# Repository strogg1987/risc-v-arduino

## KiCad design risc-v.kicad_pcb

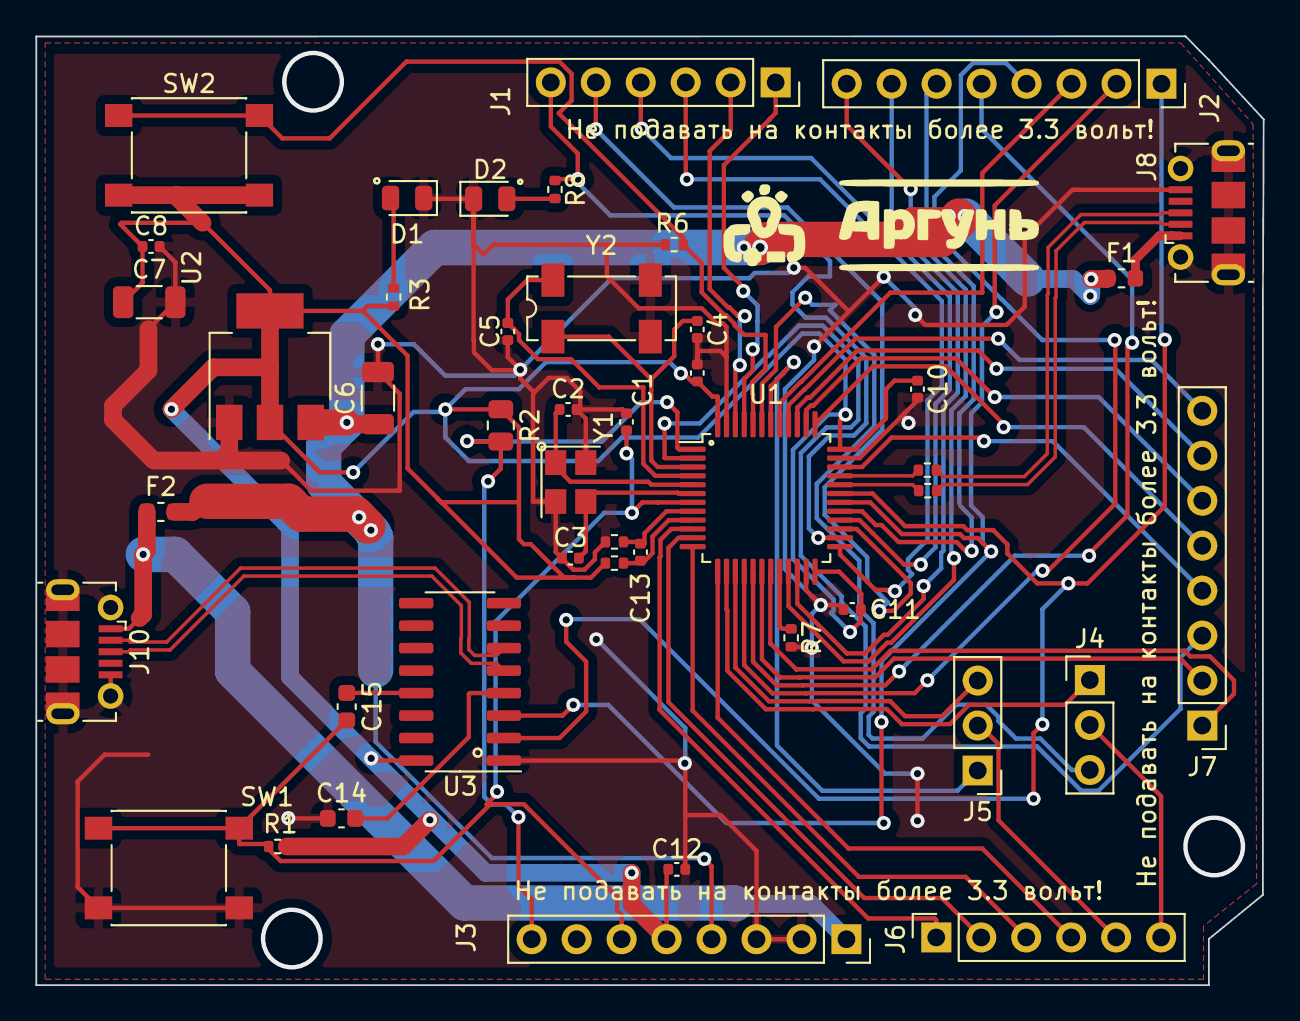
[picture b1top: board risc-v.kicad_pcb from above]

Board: 2 copper layers, 69.3 x 53.6 mm, 45 parts (0 on the bottom side), 57 nets.

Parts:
C1, C8, C9, C10, C11, C12, C13: 100nF; C_0402_1005Metric
C2, C3: 8pF; C_0402_1005Metric
C4, C5: 6pF; C_0402_1005Metric
C6, C7: 10uF; C_1206_3216Metric
C14, C15: 0.1uF; C_0603_1608Metric
D1, D2: LED; LED_0805_2012Metric
F1: 6V 2A; Fuse_0603_1608Metric
F2: Fuse_Small; Fuse_0603_1608Metric
FB1, FB2: CBW100505U601T; R_0402_1005Metric
J1: Conn_pin13:pin8; PinSocket_1x06_P2.54mm_Vertical
J2: conn_pin7:pin0; PinSocket_1x08_P2.54mm_Vertical
J3: analog5:0; PinSocket_1x06_P2.54mm_Vertical
J4: selector_a5; PinHeader_1x03_P2.54mm_Vertical
J5: selector_a4; PinHeader_1x03_P2.54mm_Vertical
J6: powerline; PinSocket_1x08_P2.54mm_Vertical
J7: extra pins; PinHeader_1x08_P2.54mm_Vertical
J8, J10: USB-FS; USB_Micro-B_Molex-105017-0001
R1, R6, R7: 10k; R_0402_1005Metric
R2: R; R_0805_2012Metric
R3, R8: 2k; R_0402_1005Metric
R4, R5: 22R; R_0402_1005Metric
SW1, SW2: SW_Push_Dual 6x6 smd; SW_Push_1P1T_NO_6x6mm_H9.5mm
U1: gd32vf103cbt6; LQFP-48_7x7mm_P0.5mm
U2: AMS1117-3.3; SOT-223-3_TabPin2
U3: CH340C; SOIC-16_3.9x9.9mm_P1.27mm
Y1: 8Mhz; Crystal_SMD_3225-4Pin_3.2x2.5mm
Y2: 32Khz RTC; Crystal_SMD_SeikoEpson_MC306-4Pin_8.0x3.2mm

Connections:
+3V3: C7.1, C8.1, C9.1, C10.1, C11.1, C12.1, FB1.2, J6.5, R1.2, R2.1, R3.1, SW2.2, U1.24 (Vdd_1), U1.36 (Vdd_2), U1.48 (Vdd_3), U2.2 (VO), U3.16 (VCC)
+5V: C6.1, F1.1, F2.2, J6.4, U2.3 (VI)
/USB+: R4.2, U1.33 (pa12)
/USB-: R5.1, U1.32 (pa11)
/Vbat: J6.8, R2.2, U1.1 (Vbat)
/Vin: F2.1, J6.1, J10.1 (VBUS)
/a0: J3.1, U1.10 (pa0-wkup)
/a1: J3.2, U1.11 (pa1)
/a2: J3.3, U1.12 (pa2)
/a3: J3.4, U1.13 (pa3)
/a4: J4.1, U1.14 (pa4)
/a5: J5.3, U1.15 (pa5)
/boot0: R6.1, SW2.1, U1.44 (boot0)
/boot1: R7.1, U1.20 (pb2)
/jrst: J7.8, U1.40 (pb4)
/jtck: J7.5, U1.37 (pa14)
/jtdi: J7.6, U1.38 (pa15)
/jtdo: J7.7, U1.39 (pb3)
/jtms: J7.4, U1.34 (pa13)
/osc32in: C4.1, U1.3 (pc14/osc32-in), Y2.1
/osc32out: C5.1, U1.4 (pc15/osc32-out), Y2.4
/oscin: C2.1, U1.5 (oscin), Y1.1
/oscout: C3.2, U1.6 (oscout), Y1.3
/pa6: J2.4, U1.16 (pa6)
/pa7: J2.5, U1.17 (pa7)
/pb0: J7.2, U1.18 (pb0)
/pb1: J7.1, U1.19 (pb1)
/pb5: J2.3, U1.41 (pb5)
/pc13: J7.3, U1.2 (pc13/tamper-rtc)
/pin0: J2.1, U1.31 (pa10), U3.2 (TXD)
/pin1: J2.2, U1.30 (pa9), U3.3 (RXD)
/pin5: J2.6, U1.29 (pa8)
/pin6: J2.7, U1.22 (pb11)
/pin7: J2.8, U1.21 (pb10)
/pin8: J1.1, U1.45 (pb8)
/pin9: J1.2, U1.46 (pb9)
/psi1_ss: J1.3, U1.25 (pb12)
/rst: C1.1, C15.2, J6.6, R1.1, SW1.1, U1.7 (nrst)
/scl0: J5.1, U1.42 (pb6)
/sda0: J4.3, U1.43 (pb7)
/spi1_miso: J1.5, U1.27 (pb14)
/spi1_mosi: J1.4, U1.28 (pb15)
/spi1_sck: J1.6, R8.1, U1.26 (pb13)
/uart+: J10.3 (D+), U3.5 (UD+)
/uart-: J10.2 (D-), U3.6 (UD-)
/usb-r+: J8.3 (D+), R4.1
/usb-r-: J8.2 (D-), R5.2
GND: C1.2, C2.2, C3.1, C4.2, C5.2, C6.2, C7.2, C8.2, C9.2, C10.2, C11.2, C12.2, C14.1, D1.1 (K), D2.1 (K), FB2.2, J6.2, J6.3, J8.5 (GND), J8.6 (Shield), J10.5 (GND), J10.6 (Shield), R6.2, R7.2, SW1.2, U1.23 (Vss_1), U1.35 (Vss_2), U1.47 (Vss_3), U2.1 (GND), U3.1 (GND), Y1.2, Y1.4, Y2.2, Y2.3
unnamed: C14.2, U3.4 (V3)
unnamed: C15.1, U3.13 (~DTR)
unnamed: D1.2 (A), R3.2
unnamed: D2.2 (A), R8.2
unnamed: F1.2, J8.1 (VBUS)
unnamed: J3.5, J5.2
unnamed: J3.6, J4.2
VDDA: C13.1, FB1.1, U1.9 (Vdda)
VSSA: C13.2, FB2.1, U1.8 (Vssa)
